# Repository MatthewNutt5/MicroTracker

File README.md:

# MicroTracker
Handheld, battery-powered music sequencer and synthesizer.

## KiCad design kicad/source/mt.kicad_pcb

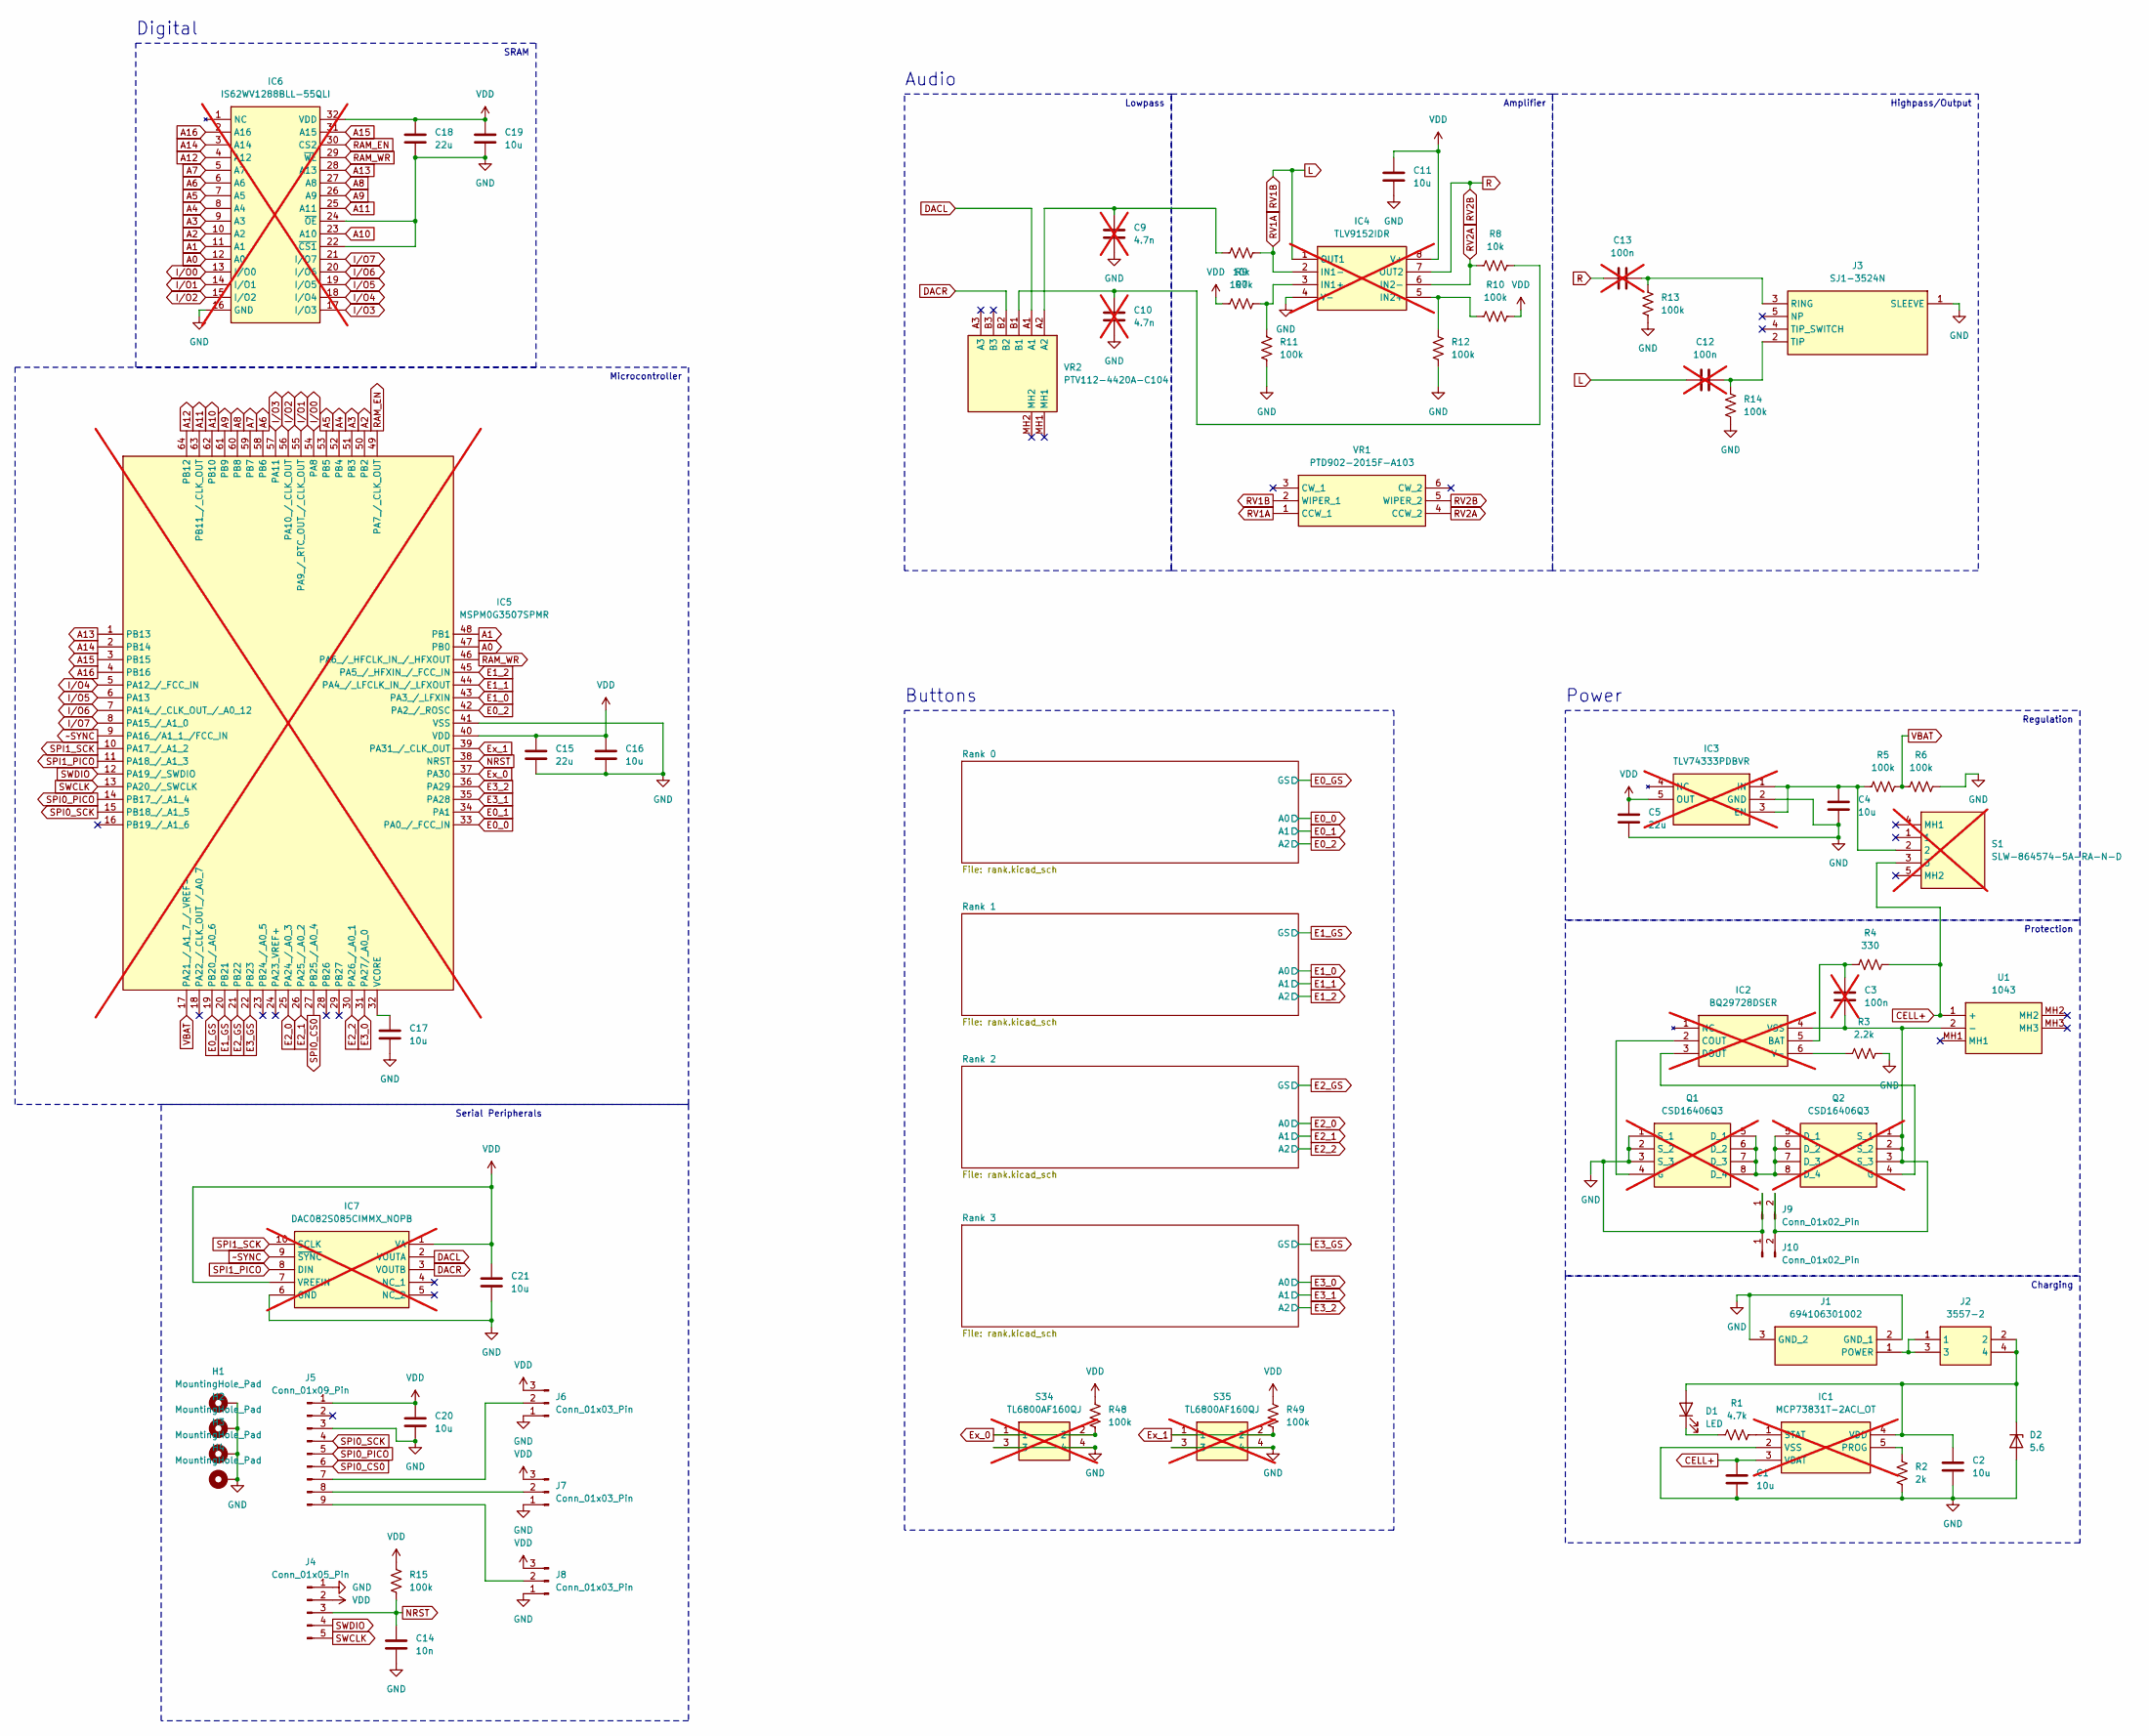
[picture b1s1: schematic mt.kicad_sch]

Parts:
C1, C2, C4, C11, C16, C17, C19, C20, C21: 10u; C_0402_1005Metric; JLCPCB C15525
C3, C12, C13: 100n; C_1206_3216Metric_Pad1.33x1.80mm_HandSolder; JLCPCB C97946; not fitted
C5, C15, C18: 22u; C_0603_1608Metric; JLCPCB C59461
C9, C10: 4.7n; C_0603_1608Metric_Pad1.08x0.95mm_HandSolder; JLCPCB C1518204; not fitted
C14: 10n; C_0402_1005Metric; JLCPCB C15195
D1: LED; LED_D5.0mm
D2: 5.6; D_SOD-123; JLCPCB C173406
H1, H2, H3, H4: MountingHole_Pad; MountingHole_3.2mm_M3_Pad_Via
IC1: MCP73831T-2ACI_OT; SOT95P270X145-5N; Mouser Part Number 579-MCP73831T-2ACIOT; not fitted
IC2: BQ29728DSER; Mouser Part Number 595-BQ29728DSER; not fitted
IC3: TLV74333PDBVR; SOT95P280X145-5N; Mouser Part Number 595-TLV74333PDBVR; not fitted
IC4: TLV9152IDR; SOIC127P600X175-8N; Mouser Part Number 595-TLV9152IDR; not fitted
IC5: MSPM0G3507SPMR; QFP50P1200X1200X160-64N; Mouser Part Number 595-MSPM0G3507SPMR; not fitted
IC6: IS62WV1288BLL-55QLI; SOIC127P1412X300-32N; Mouser Part Number 87062WV1288BLL55QLI; not fitted
IC7: DAC082S085CIMMX_NOPB; SOP50P490X110-10N; Mouser Part Number 926-D082S085CIMMXNPB; not fitted
J1: 694106301002; 694106301002_1; Mouser Part Number 710-694106301002
J2: 3557-2; Mouser Part Number 534-3557-2
J3: SJ1-3524N; SJ13524N; Mouser Part Number 490-SJ1-3524N
J4: Conn_01x05_Pin; PinHeader_1x05_P2.54mm_Horizontal
J5: Conn_01x09_Pin; PinSocket_1x09_P2.54mm_Vertical
J6, J7, J8: Conn_01x03_Pin; PinHeader_1x03_P2.54mm_Vertical
J9, J10: Conn_01x02_Pin; PinHeader_1x02_P2.54mm_Vertical
Q1, Q2: CSD16406Q3; DQG_VSON-CLIP; Mouser Part Number 595-CSD16406Q3; not fitted
R1: 4.7k; R_0402_1005Metric; JLCPCB C25900
R2: 2k; R_0402_1005Metric; JLCPCB C4109
R3: 2.2k; R_0402_1005Metric; JLCPCB C25879
R4: 330; R_0402_1005Metric; JLCPCB C25104
R5, R6, R9, R10, R11, R12, R13, R14, R15, R48, R49: 100k; R_0402_1005Metric; JLCPCB C25741
R7, R8: 10k; R_0402_1005Metric; JLCPCB C25744
S1: SLW-864574-5A-RA-N-D; SLW8645745ARAND; Mouser Part Number 179-SLW8645745ARAND; not fitted
S34, S35: TL6800AF160QJ; Mouser Part Number 612-TL6800AF160QG; not fitted
U1: 1043; Mouser Part Number 534-1043
VR1: PTD902-2015F-A103; PTD9022015FA103; Mouser Part Number 652-PTD902-2015FA103
VR2: PTV112-4420A-C104; PTV1124420AC104; Mouser Part Number 652-PTV1124420AC104

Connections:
A0: IC5.47 (PB0), IC6.12 (A0)
A1: IC5.48 (PB1), IC6.11 (A1)
A2: IC5.50 (PB2), IC6.10 (A2)
A3: IC5.51 (PB3), IC6.9 (A3)
A4: IC5.52 (PB4), IC6.8 (A4)
A5: IC5.53 (PB5), IC6.7 (A5)
A6: IC5.58 (PB6), IC6.6 (A6)
A7: IC5.59 (PB7), IC6.5 (A7)
A8: IC5.60 (PB8), IC6.27 (A8)
A9: IC5.61 (PB9), IC6.26 (A9)
A10: IC5.62 (PB10), IC6.23 (A10)
A11: IC5.63 (PB11_/_CLK_OUT), IC6.25 (A11)
A12: IC5.64 (PB12), IC6.4 (A12)
A13: IC5.1 (PB13), IC6.28 (A13)
A14: IC5.2 (PB14), IC6.3 (A14)
A15: IC5.3 (PB15), IC6.31 (A15)
A16: IC5.4 (PB16), IC6.2 (A16)
CELL+: C1.1, IC1.3 (VBAT), R4.1, S1.3, U1.1 (+)
DACL: IC7.2 (VOUTA), VR2.A1
DACR: IC7.3 (VOUTB), VR2.B2
E0_0: IC5.33 (PA0_/_FCC_IN); also elsewhere on the board
E0_1: IC5.34 (PA1); also elsewhere on the board
E0_2: IC5.42 (PA2_/_ROSC); also elsewhere on the board
E0_GS: IC5.19 (PB20_/_A0_6); also elsewhere on the board
E1_0: IC5.43 (PA3_/_LFXIN); also elsewhere on the board
E1_1: IC5.44 (PA4_/_LFCLK_IN_/_LFXOUT); also elsewhere on the board
E1_2: IC5.45 (PA5_/_HFXIN_/_FCC_IN); also elsewhere on the board
E1_GS: IC5.20 (PB21); also elsewhere on the board
E2_0: IC5.25 (PA24_/_A0_3); also elsewhere on the board
E2_1: IC5.26 (PA25_/_A0_2); also elsewhere on the board
E2_2: IC5.30 (PA26_/_A0_1); also elsewhere on the board
E2_GS: IC5.21 (PB22); also elsewhere on the board
E3_0: IC5.31 (PA27/_A0_0); also elsewhere on the board
E3_1: IC5.35 (PA28); also elsewhere on the board
E3_2: IC5.36 (PA29); also elsewhere on the board
E3_GS: IC5.22 (PB23); also elsewhere on the board
Ex_0: IC5.37 (PA30), R48.2, S34.1, S34.2
Ex_1: IC5.39 (PA31_/_CLK_OUT), R49.2, S35.1, S35.2
GND: C1.2, C2.2, C4.2, C5.2, C9.2, C10.2, C11.2, C14.2, C15.2, C16.2, C17.2, C18.2, C19.2, C20.2, C21.2, D2.2 (A), H1.1, H2.1, H3.1, H4.1, IC1.2 (VSS), IC3.2 (GND), IC4.4 (V-), IC5.41 (VSS), IC6.16 (GND), IC6.22 (~CS1), IC6.24 (~OE), IC7.6 (GND), J1.2 (GND_1), J1.3 (GND_2), J3.1 (SLEEVE), J4.1, J5.3, J6.1, J7.1, J8.1, J9.1, J10.1, Q1.1 (S_1), Q1.2 (S_2), Q1.3 (S_3), R2.2, R3.1, R6.2, R11.2, R12.1, R13.2, R14.2, S34.3, S34.4, S35.3, S35.4; also elsewhere on the board
I/O0: IC5.54 (PA8), IC6.13 (I/O0)
I/O1: IC5.55 (PA9_/_RTC_OUT_/_CLK_OUT), IC6.14 (I/O1)
I/O2: IC5.56 (PA10_/_CLK_OUT), IC6.15 (I/O2)
I/O3: IC5.57 (PA11), IC6.17 (I/O3)
I/O4: IC5.5 (PA12_/_FCC_IN), IC6.18 (I/O4)
I/O5: IC5.6 (PA13), IC6.19 (I/O5)
I/O6: IC5.7 (PA14_/_CLK_OUT_/_A0_12), IC6.20 (I/O6)
I/O7: IC5.8 (PA15_/_A1_0), IC6.21 (I/O7)
L: C12.1, IC4.1 (OUT1), VR1.2 (WIPER_1)
NRST: C14.1, IC5.38 (NRST), J4.3, R15.2
unnamed: C9.1, R7.1, VR2.A2
unnamed: C10.1, R8.1, VR2.B1
unnamed: C2.1, D1.2 (A), D2.1 (K), IC1.4 (VDD), J2.2, J2.4
unnamed: D1.1 (K), R1.1
unnamed: IC1.5 (PROG), R2.1
unnamed: IC1.1 (STAT), R1.2
unnamed: C3.1, IC2.5 (BAT), R4.2
unnamed: IC2.2 (COUT), Q1.4 (G)
unnamed: IC2.3 (DOUT), Q2.4 (G)
unnamed: IC2.6 (V-), R3.2
unnamed: C3.2, IC2.4 (VSS), J9.2, J10.2, Q2.1 (S_1), Q2.2 (S_2), Q2.3 (S_3), U1.2 (-)
unnamed: C4.1, IC3.1 (IN), IC3.3 (EN), R5.2, S1.2
unnamed: IC4.3 (IN1+), R9.2, R11.1
unnamed: IC4.5 (IN2+), R10.1, R12.2
unnamed: C17.1, IC5.32 (VCORE)
unnamed: J1.1 (POWER), J2.1, J2.3
unnamed: C13.2, J3.3 (RING), R13.1
unnamed: C12.2, J3.2 (TIP), R14.1
unnamed: J5.7, J6.2
unnamed: J5.8, J7.2
unnamed: J5.9, J8.2
unnamed: Q1.5 (D_1), Q1.6 (D_2), Q1.7 (D_3), Q1.8 (D_4), Q2.5 (D_1), Q2.6 (D_2), Q2.7 (D_3), Q2.8 (D_4)
R: C13.1, IC4.7 (OUT2), VR1.5 (WIPER_2)
RAM_EN: IC5.49 (PA7_/_CLK_OUT), IC6.30 (CS2)
RAM_WR: IC5.46 (PA6_/_HFCLK_IN_/_HFXOUT), IC6.29 (~WE)
RV1A: IC4.2 (IN1-), R7.2, VR1.1 (CCW_1)
RV2A: IC4.6 (IN2-), R8.2, VR1.4 (CCW_2)
SPI0_CS0: IC5.27 (PB25_/_A0_4), J5.6
SPI0_PICO: IC5.14 (PB17_/_A1_4), J5.5
SPI0_SCK: IC5.15 (PB18_/_A1_5), J5.4
SPI1_PICO: IC5.11 (PA18_/_A1_3), IC7.8 (DIN)
SPI1_SCK: IC5.10 (PA17_/_A1_2), IC7.10 (SCLK)
SWCLK: IC5.13 (PA20_/_SWCLK), J4.5
SWDIO: IC5.12 (PA19_/_SWDIO), J4.4
VBAT: IC5.17 (PA21_/_A1_7_/_VREF-), R5.1, R6.1
VDD: C5.1, C11.1, C15.1, C16.1, C18.1, C19.1, C20.1, C21.1, IC3.5 (OUT), IC4.8 (V+), IC5.40 (VDD), IC6.32 (VDD), IC7.1 (VA), IC7.7 (VREFIN), J4.2, J5.1, J6.3, J7.3, J8.3, R9.1, R10.2, R15.1, R48.1, R49.1; also elsewhere on the board
~SYNC: IC5.9 (PA16_/A1_1_/FCC_IN), IC7.9 (~SYNC)

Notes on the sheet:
Audio
Charging
Highpass/Output
SRAM
Protection
Buttons
Amplifier
Microcontroller
Power
Serial Peripherals
Regulation
Lowpass
Digital

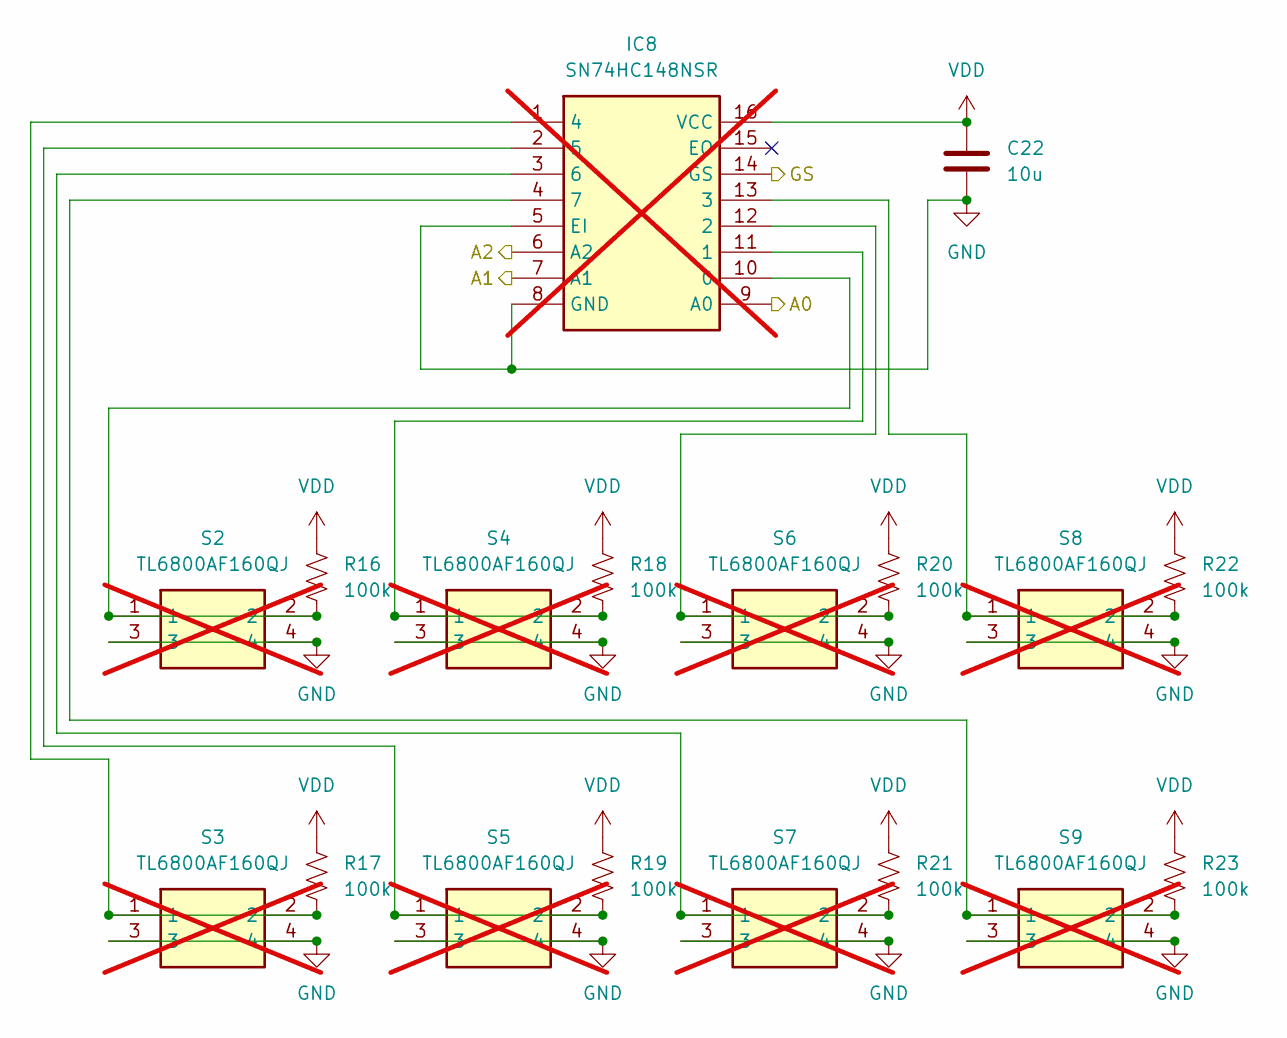
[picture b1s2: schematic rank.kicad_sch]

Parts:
C22: 10u; C_0402_1005Metric; JLCPCB C15525
IC8: SN74HC148NSR; SOIC127P780X200-16N; Mouser Part Number 595-SN74HC148NSR; not fitted
R16, R17, R18, R19, R20, R21, R22, R23: 100k; R_0402_1005Metric; JLCPCB C25741
S2, S3, S4, S5, S6, S7, S8, S9: TL6800AF160QJ; Mouser Part Number 612-TL6800AF160QG; not fitted

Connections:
E0_0: IC8.9 (A0); also elsewhere on the board
E0_1: IC8.7 (A1); also elsewhere on the board
E0_2: IC8.6 (A2); also elsewhere on the board
E0_GS: IC8.14 (GS); also elsewhere on the board
GND: C22.2, IC8.5 (EI), IC8.8 (GND), S2.3, S2.4, S3.3, S3.4, S4.3, S4.4, S5.3, S5.4, S6.3, S6.4, S7.3, S7.4, S8.3, S8.4, S9.3, S9.4; also elsewhere on the board
unnamed: IC8.10 (0), R16.2, S2.1, S2.2
unnamed: IC8.11 (1), R18.2, S4.1, S4.2
unnamed: IC8.12 (2), R20.2, S6.1, S6.2
unnamed: IC8.13 (3), R22.2, S8.1, S8.2
unnamed: IC8.1 (4), R17.2, S3.1, S3.2
unnamed: IC8.2 (5), R19.2, S5.1, S5.2
unnamed: IC8.3 (6), R21.2, S7.1, S7.2
unnamed: IC8.4 (7), R23.2, S9.1, S9.2
VDD: C22.1, IC8.16 (VCC), R16.1, R17.1, R18.1, R19.1, R20.1, R21.1, R22.1, R23.1; also elsewhere on the board

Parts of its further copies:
C23, C24, C25: 10u; C_0402_1005Metric; JLCPCB C15525
IC9, IC10, IC11: SN74HC148NSR; SOIC127P780X200-16N; Mouser Part Number 595-SN74HC148NSR; not fitted
R24, R25, R26, R27, R28, R29, R30, R31, R32, R33, R34, R35, R36, R37, R38, R39, R40, R41, R42, R43, R44, R45, R46, R47: 100k; R_0402_1005Metric; JLCPCB C25741
S10, S11, S12, S13, S14, S15, S16, S17, S18, S19, S20, S21, S22, S23, S24, S25, S26, S27, S28, S29, S30, S31, S32, S33: TL6800AF160QJ; Mouser Part Number 612-TL6800AF160QG; not fitted

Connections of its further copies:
E1_0: IC9.9 (A0); also elsewhere on the board
E1_1: IC9.7 (A1); also elsewhere on the board
E1_2: IC9.6 (A2); also elsewhere on the board
E1_GS: IC9.14 (GS); also elsewhere on the board
E2_0: IC10.9 (A0); also elsewhere on the board
E2_1: IC10.7 (A1); also elsewhere on the board
E2_2: IC10.6 (A2); also elsewhere on the board
E2_GS: IC10.14 (GS); also elsewhere on the board
E3_0: IC11.9 (A0); also elsewhere on the board
E3_1: IC11.7 (A1); also elsewhere on the board
E3_2: IC11.6 (A2); also elsewhere on the board
E3_GS: IC11.14 (GS); also elsewhere on the board
GND: C23.2, C24.2, C25.2, IC9.5 (EI), IC9.8 (GND), IC10.5 (EI), IC10.8 (GND), IC11.5 (EI), IC11.8 (GND), S10.3, S10.4, S11.3, S11.4, S12.3, S12.4, S13.3, S13.4, S14.3, S14.4, S15.3, S15.4, S16.3, S16.4, S17.3, S17.4, S18.3, S18.4, S19.3, S19.4, S20.3, S20.4, S21.3, S21.4, S22.3, S22.4, S23.3, S23.4, S24.3, S24.4, S25.3, S25.4, S26.3, S26.4, S27.3, S27.4, S28.3, S28.4, S29.3, S29.4, S30.3, S30.4, S31.3, S31.4, S32.3, S32.4, S33.3, S33.4; also elsewhere on the board
unnamed: IC9.10 (0), R24.2, S10.1, S10.2
unnamed: IC9.11 (1), R26.2, S12.1, S12.2
unnamed: IC9.12 (2), R28.2, S14.1, S14.2
unnamed: IC9.13 (3), R30.2, S16.1, S16.2
unnamed: IC9.1 (4), R25.2, S11.1, S11.2
unnamed: IC9.2 (5), R27.2, S13.1, S13.2
unnamed: IC9.3 (6), R29.2, S15.1, S15.2
unnamed: IC9.4 (7), R31.2, S17.1, S17.2
unnamed: IC10.10 (0), R32.2, S18.1, S18.2
unnamed: IC10.11 (1), R34.2, S20.1, S20.2
unnamed: IC10.12 (2), R36.2, S22.1, S22.2
unnamed: IC10.13 (3), R38.2, S24.1, S24.2
unnamed: IC10.1 (4), R33.2, S19.1, S19.2
unnamed: IC10.2 (5), R35.2, S21.1, S21.2
unnamed: IC10.3 (6), R37.2, S23.1, S23.2
unnamed: IC10.4 (7), R39.2, S25.1, S25.2
unnamed: IC11.10 (0), R40.2, S26.1, S26.2
unnamed: IC11.11 (1), R42.2, S28.1, S28.2
unnamed: IC11.12 (2), R44.2, S30.1, S30.2
unnamed: IC11.13 (3), R46.2, S32.1, S32.2
unnamed: IC11.1 (4), R41.2, S27.1, S27.2
unnamed: IC11.2 (5), R43.2, S29.1, S29.2
unnamed: IC11.3 (6), R45.2, S31.1, S31.2
unnamed: IC11.4 (7), R47.2, S33.1, S33.2
VDD: C23.1, C24.1, C25.1, IC9.16 (VCC), IC10.16 (VCC), IC11.16 (VCC), R24.1, R25.1, R26.1, R27.1, R28.1, R29.1, R30.1, R31.1, R32.1, R33.1, R34.1, R35.1, R36.1, R37.1, R38.1, R39.1, R40.1, R41.1, R42.1, R43.1, R44.1, R45.1, R46.1, R47.1; also elsewhere on the board

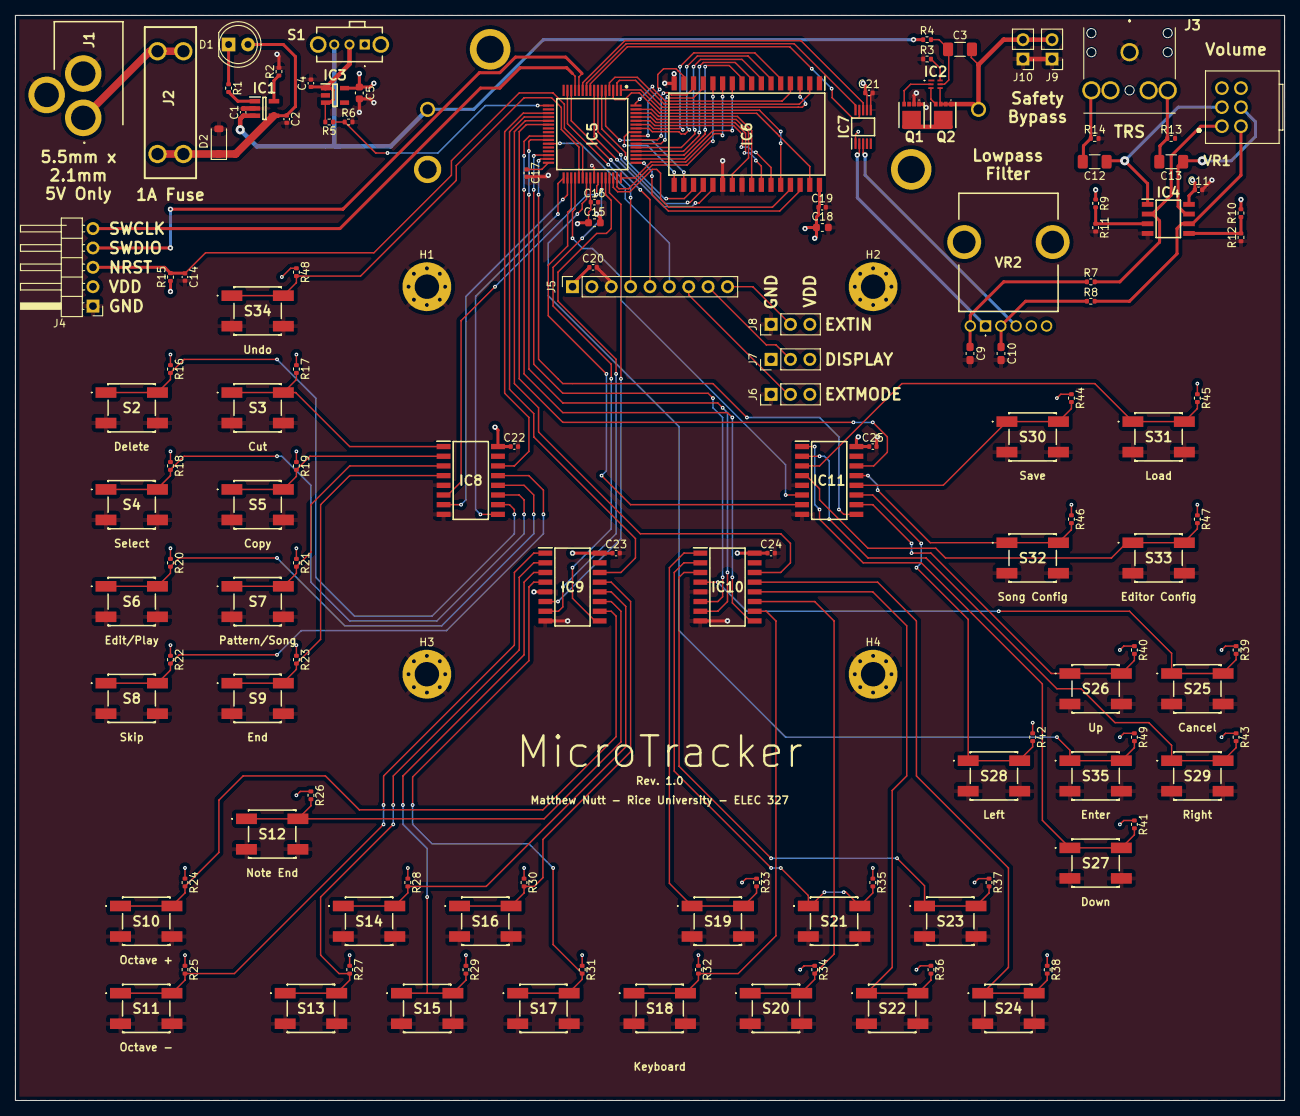
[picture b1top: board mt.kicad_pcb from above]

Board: 4 copper layers, 166.4 x 142.2 mm, 138 parts (1 on the bottom side), 118 nets.

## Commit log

2025-04-03 added kicad files, gitignore
2025-04-04 completed power electronics schematic
2025-04-04 revised power electronics caps, added JLCPCB part numbers to SMD power electronics
2025-04-04 completed audio electronics schematic
2025-04-04 revised audio electronics volume pot
2025-04-07 revised some passives, started digital electronics schematic
2025-04-08 started sram schematic
2025-04-08 simplified power electronics
2025-04-08 completed full schematic
2025-04-09 configured PCB with 4-layer stackup and JLCPCB DRC rules
2025-04-09 added input OVP, screen config jumpers
2025-04-09 configured PCB trace/via sizes
2025-04-10 removed unnecessary files, updated gitignore
2025-04-10 removed untracked files
2025-04-14 started routing SRAM on PCB
2025-04-15 completed SRAM routing, started power electronics routing
2025-04-15 completed power electronics routing, fixed battery holder model
2025-04-15 completed analog electronics routing
2025-04-16 completed peripherals routing, set up zone fills
2025-04-16 converted button ranks to hierarchical schematics, prepared button layout pattern
2025-04-16 completed buttons arrangement
2025-04-16 completed button-encoder routing
2025-04-16 started encoder-microcontroller routing
2025-04-16 completed all routing
2025-04-16 misc adjustments
2025-04-17 completed PCB fab setup
2025-04-17 adjusted PCB fab setup for faster manufacturing
2025-04-17 reorganized files
2025-05-06 added source code files, implemented DAC support
2025-05-09 implemented sampling architecture, added basic mixing test
2025-05-09 refactored initialization
